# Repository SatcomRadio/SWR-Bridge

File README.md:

# SWR measurement board

This repo consists of a board for measuring SWR. It works up to 500mhz and 1kW of power in HF.  
The pickup lines are 20 db attenuated.  

You can connect it to an arduino and measure the FWD and reflected power.

The potentiometers allow to calibrate the maximum power seen at the FWD and REF   
ports so you can get more resolution at higher or lower RF power levels.

*Keep the 2 potentiometers at the same resistance value*

------------------------

## BOM:

```
- PCB that you can order ar jlcpcb or somewhere else.
- 2x SMD 3224W 10k potentiometers. You can use 5k if you plan to measure low power. (https://aliexpress.com/item/1005009122898646.html)
- 2x 1206 50 ohm resistor (https://aliexpress.com/item/1005008118472536.html)
	alternatively, you can use 4x 100 ohm 1206 resistors.
- 4x 1206 100nF 200v NPO Capacitor (https://aliexpress.com/item/1005007149614327.html)
- 2x 1206 1k ohm resistor
- 2x 1206 10k ohm resistor
- 2x MMSD701T1G Diode (https://aliexpress.com/item/1005008691014348.html)
- 2x SMA SMA-KE 13.5MM connectors (https://aliexpress.com/item/1005007424915378.html)
```

------------------------

## Reading the SWR in a Arduino

**Important, this section is currently work in progress and the code might change**

You can order an arduino UNO board along with a [LCD shield](https://es.aliexpress.com/item/32475515474.html) to read the millivolts.

Before doing so, push the maximum power of your radio trough the SWR board and to a dummy load.  
While doing so, adjust the potentiometer with a multimeter so the volts in the FWD line are lower than 4.5v  
as that will avoid burning the arduino ADC.  
  
You can check the sample code for the arduino in the Arduino folder of the repo.  

------------------------

## Ordering the PCB:

Download the Gerber file from this repo and order it a jlcpcb with the default options.  
The only option I've changed is to remove the manufacture code mark

#### Please make sure to visit the [satcom radio website](https://satcomradio.github.io/) for more information

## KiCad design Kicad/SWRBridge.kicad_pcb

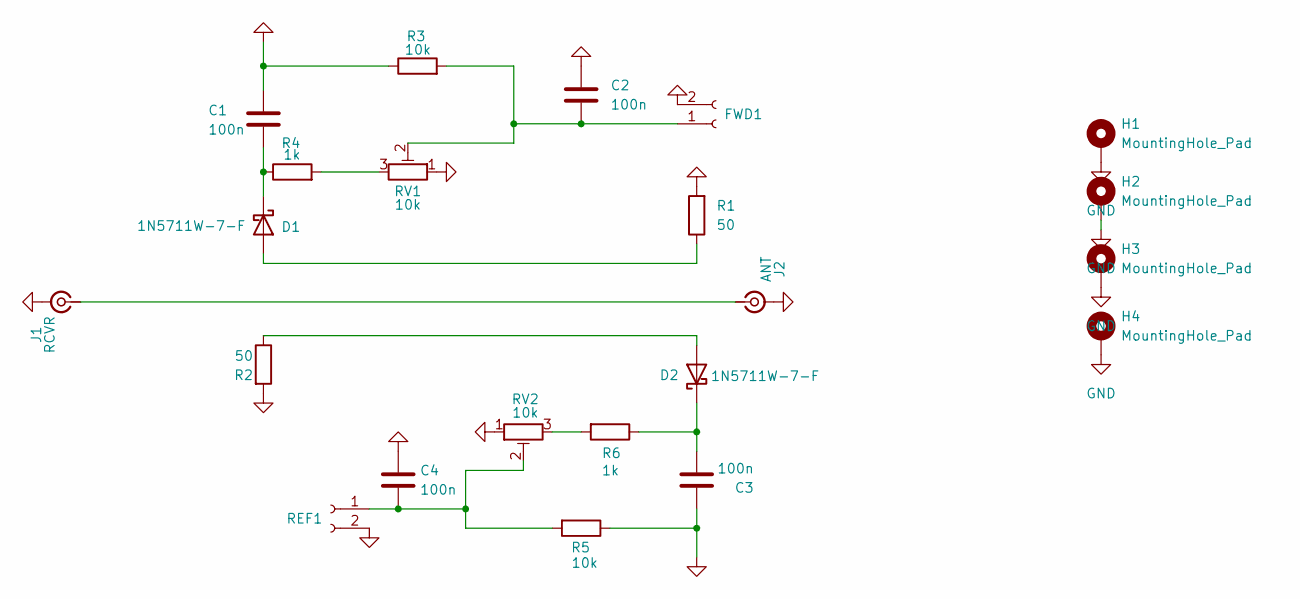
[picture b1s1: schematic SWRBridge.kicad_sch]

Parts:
C1, C2, C3, C4: 100n; C_1206_3216Metric_Pad1.33x1.80mm_HandSolder
D1, D2: 1N5711W-7-F; Nexperia_CFP3_SOD-123W_EXPANDED
FWD1: Conn_01x02_Socket; SMA_Conn
H1, H2, H3, H4: MountingHole_Pad; MountingHole_3.2mm_M3_DIN965_Pad
J1: RCVR; RfConnector_S
J2: ANT; RfConnector_S
R1, R2: 50; R_1206_3216Metric_Pad1.30x1.75mm_HandSolder
R3, R5: 10k; R_1206_3216Metric_Pad1.30x1.75mm_HandSolder
R4, R6: 1k; R_1206_3216Metric_Pad1.30x1.75mm_HandSolder
REF1: Conn_01x02_Socket; SMA_Conn
RV1, RV2: 10k; Potentiometer_Bourns_3224W_Vertical_EXPANDED

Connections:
GND: C1.1, C2.1, C3.1, C4.1, FWD1.2, H1.1, H2.1, H3.1, H4.1, J1.2 (Ext), J2.2 (Ext), R1.2, R2.2, R3.1, R5.1, REF1.2, RV1.1, RV2.1
unnamed: D1.2 (A), R1.1
unnamed: C1.2, D1.1 (K), R4.1
unnamed: D2.2 (A), R2.1
unnamed: C3.2, D2.1 (K), R6.1
unnamed: C2.2, FWD1.1, R3.2, RV1.2
unnamed: J1.1 (In), J2.1 (In)
unnamed: R4.2, RV1.3
unnamed: R6.2, RV2.3
unnamed: C4.2, R5.2, REF1.1, RV2.2

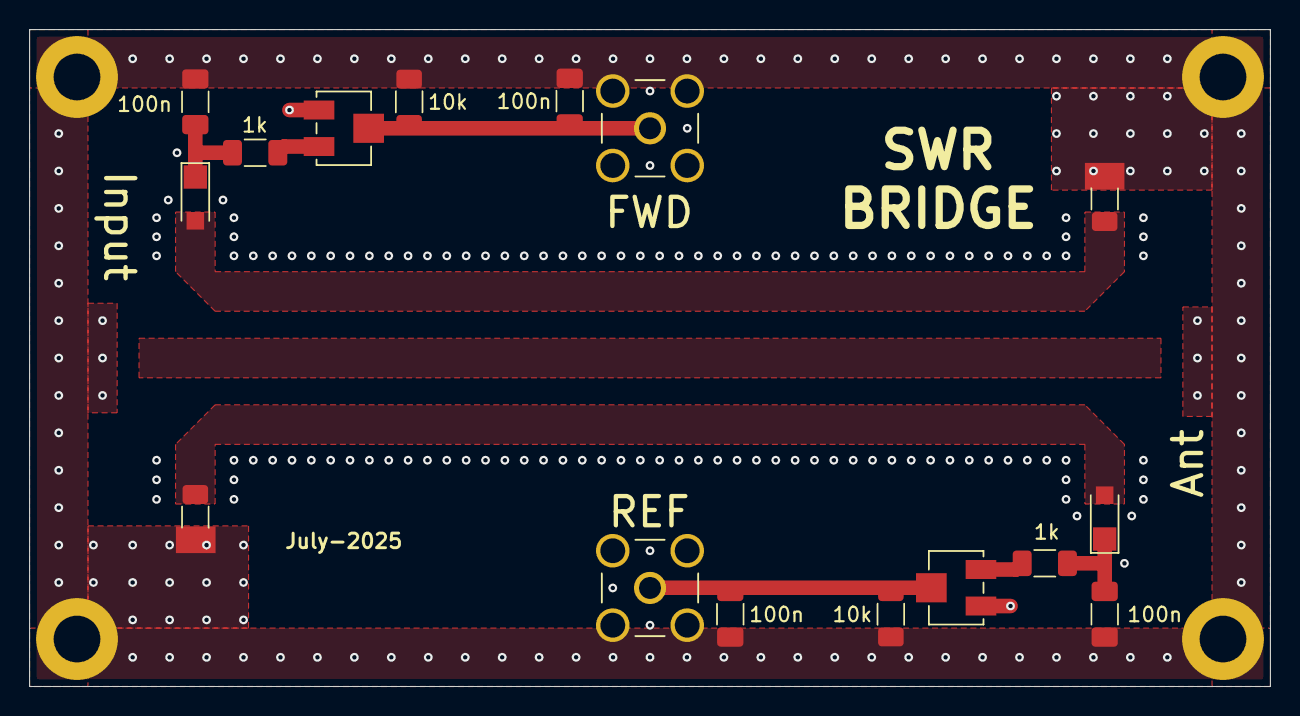
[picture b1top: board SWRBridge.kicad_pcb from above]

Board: 2 copper layers, 85.0 x 45.0 mm, 20 parts (0 on the bottom side), 9 nets.

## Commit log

2025-07-03 Added jlcpcb img
2025-07-03 Fix readme
